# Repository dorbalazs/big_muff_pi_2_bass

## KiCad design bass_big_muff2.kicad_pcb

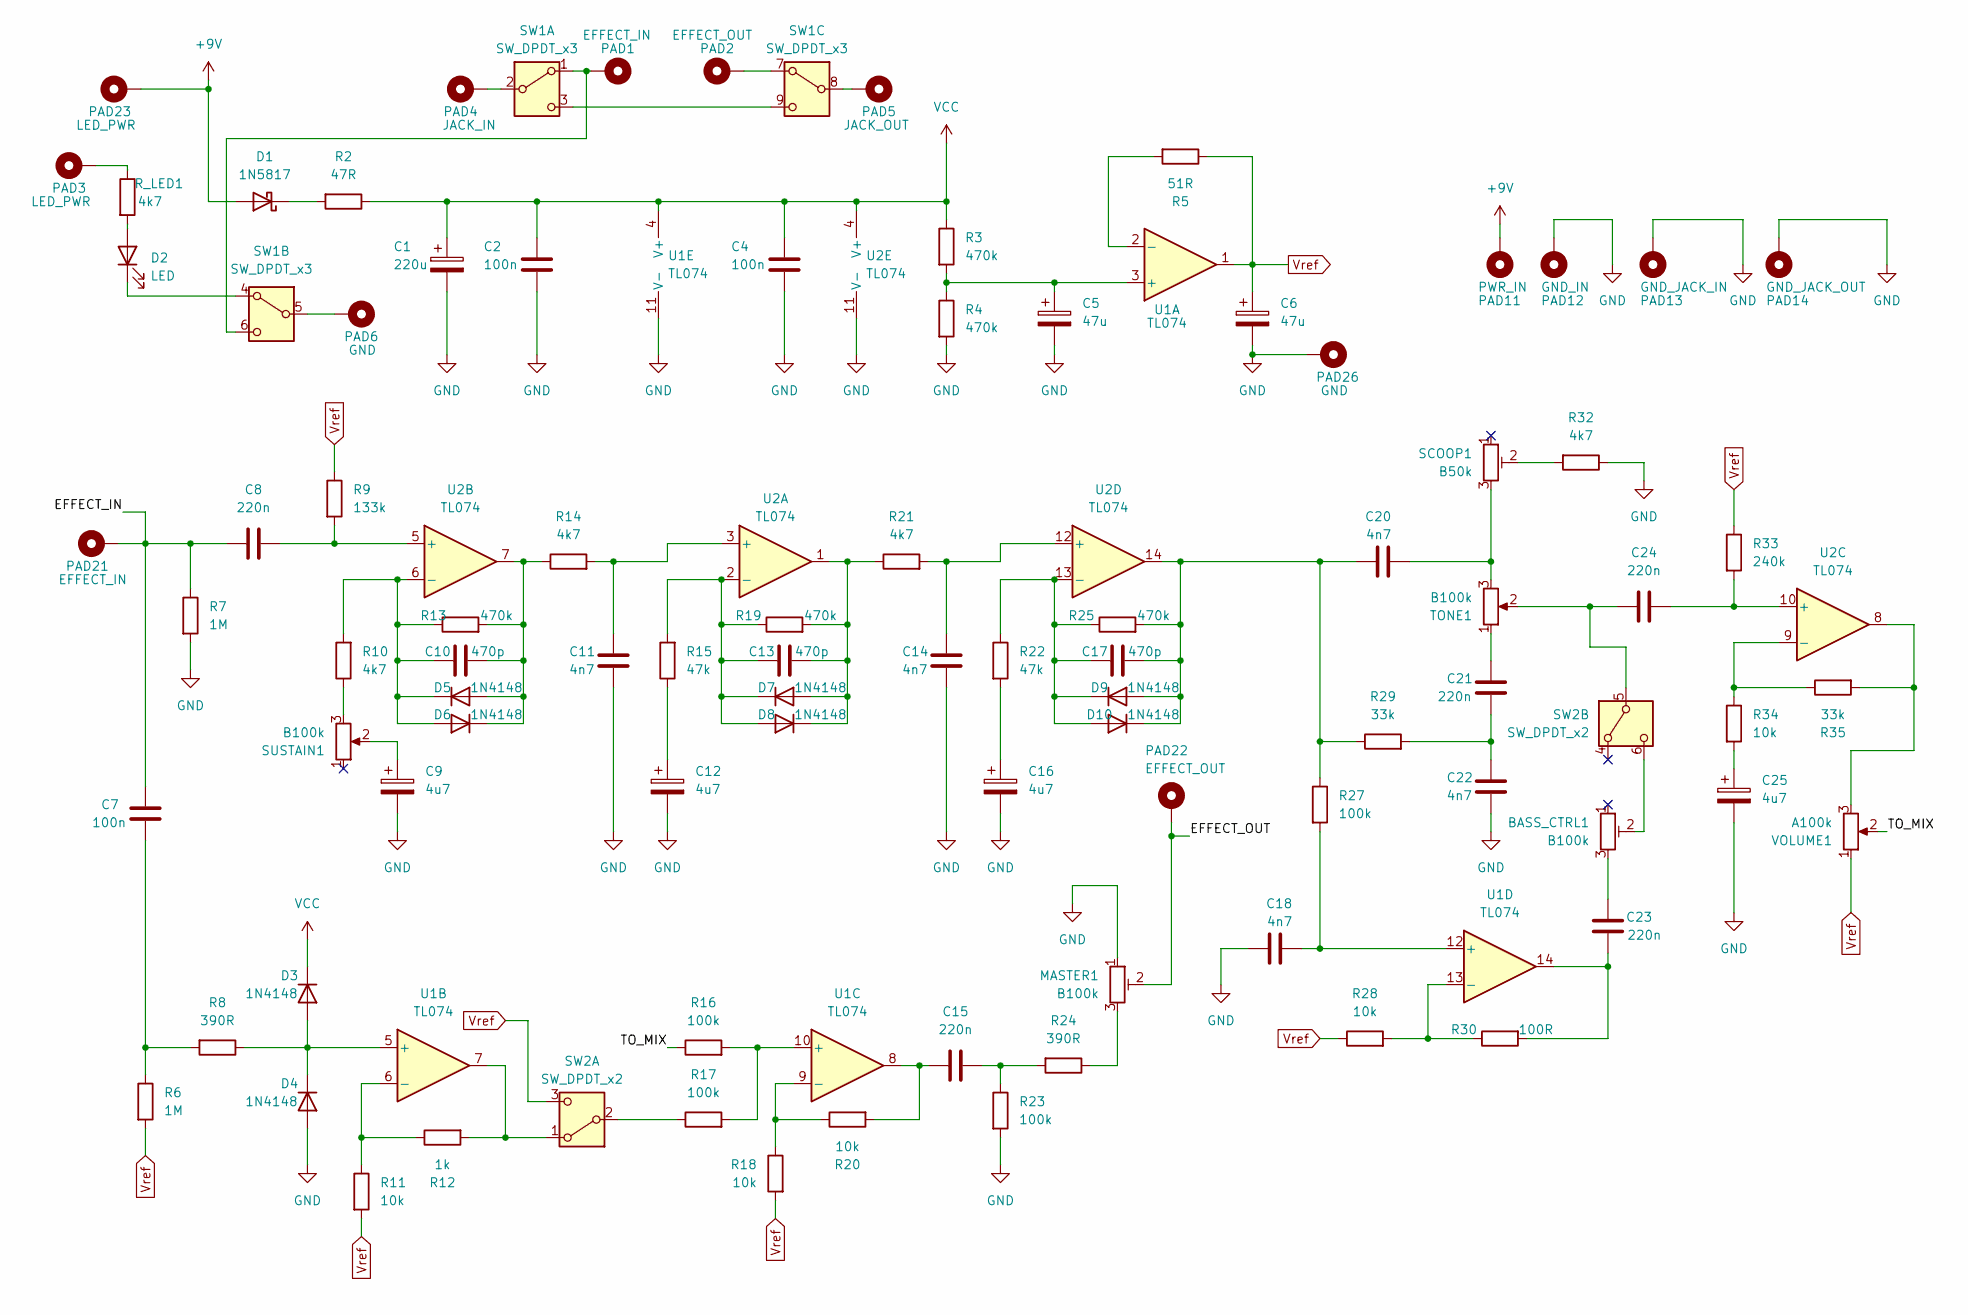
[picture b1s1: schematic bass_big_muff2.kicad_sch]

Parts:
BASS_CTRL1: B100k; Potentiometer_Runtron_RM-065_Vertical
C1: 220u; CP_Radial_D6.3mm_P2.50mm
C2, C4: 100n; C_Disc_D5.0mm_W2.5mm_P2.50mm
C5, C6: 47u; CP_Radial_D5.0mm_P2.50mm
C7: 100n; C_Rect_L7.2mm_W3.5mm_P5.00mm
C8, C15, C21, C23, C24: 220n; C_Rect_L7.2mm_W3.5mm_P5.00mm
C9, C12, C16, C25: 4u7; CP_Radial_D4.0mm_P1.50mm
C10, C13, C17: 470p; C_Disc_D3.4mm_W2.1mm_P2.50mm
C11, C14, C18, C20, C22: 4n7; C_Rect_L7.2mm_W2.5mm_P5.00mm
D1: 1N5817; D_DO-41_SOD81_P10.16mm_Horizontal
D2: LED; LED_D5.0mm
D3, D4, D5, D6, D7, D8, D9, D10: 1N4148; D_DO-35_SOD27_P7.62mm_Horizontal
MASTER1: B100k; Potentiometer_Runtron_RM-065_Vertical
PAD1, PAD21: EFFECT_IN; SolderWire-0.5sqmm_1x01_D0.9mm_OD2.1mm
PAD2, PAD22: EFFECT_OUT; SolderWire-0.5sqmm_1x01_D0.9mm_OD2.1mm
PAD3, PAD23: LED_PWR; SolderWire-0.5sqmm_1x01_D0.9mm_OD2.1mm
PAD4: JACK_IN; SolderWire-0.5sqmm_1x01_D0.9mm_OD2.1mm
PAD5: JACK_OUT; SolderWire-0.5sqmm_1x01_D0.9mm_OD2.1mm
PAD6, PAD26: GND; SolderWire-0.5sqmm_1x01_D0.9mm_OD2.1mm
PAD11: PWR_IN; SolderWire-0.5sqmm_1x01_D0.9mm_OD2.1mm
PAD12: GND_IN; SolderWire-0.5sqmm_1x01_D0.9mm_OD2.1mm
PAD13: GND_JACK_IN; SolderWire-0.5sqmm_1x01_D0.9mm_OD2.1mm
PAD14: GND_JACK_OUT; SolderWire-0.5sqmm_1x01_D0.9mm_OD2.1mm
R2: 47R; R_Axial_DIN0207_L6.3mm_D2.5mm_P7.62mm_Horizontal
R3, R4, R25: 470k; R_Axial_DIN0207_L6.3mm_D2.5mm_P7.62mm_Horizontal
R5: 51R; R_Axial_DIN0207_L6.3mm_D2.5mm_P7.62mm_Horizontal
R6, R7: 1M; R_Axial_DIN0207_L6.3mm_D2.5mm_P7.62mm_Horizontal
R8, R24: 390R; R_Axial_DIN0207_L6.3mm_D2.5mm_P7.62mm_Horizontal
R9: 133k; R_Axial_DIN0207_L6.3mm_D2.5mm_P2.54mm_Vertical
R10, R14, R32: 4k7; R_Axial_DIN0207_L6.3mm_D2.5mm_P2.54mm_Vertical
R11, R34: 10k; R_Axial_DIN0207_L6.3mm_D2.5mm_P7.62mm_Horizontal
R12: 1k; R_Axial_DIN0207_L6.3mm_D2.5mm_P7.62mm_Horizontal
R13, R19: 470k; R_Axial_DIN0207_L6.3mm_D2.5mm_P2.54mm_Vertical
R15: 47k; R_Axial_DIN0207_L6.3mm_D2.5mm_P2.54mm_Vertical
R16, R17: 100k; R_Axial_DIN0207_L6.3mm_D2.5mm_P2.54mm_Vertical
R18, R20, R28: 10k; R_Axial_DIN0207_L6.3mm_D2.5mm_P2.54mm_Vertical
R21: 4k7; R_Axial_DIN0207_L6.3mm_D2.5mm_P7.62mm_Horizontal
R22: 47k; R_Axial_DIN0207_L6.3mm_D2.5mm_P7.62mm_Horizontal
R23, R27: 100k; R_Axial_DIN0207_L6.3mm_D2.5mm_P7.62mm_Horizontal
R29, R35: 33k; R_Axial_DIN0207_L6.3mm_D2.5mm_P7.62mm_Horizontal
R30: 100R; R_Axial_DIN0207_L6.3mm_D2.5mm_P2.54mm_Vertical
R33: 240k; R_Axial_DIN0207_L6.3mm_D2.5mm_P7.62mm_Horizontal
R_LED1: 4k7; R_Axial_DIN0207_L6.3mm_D2.5mm_P7.62mm_Horizontal
SCOOP1: B50k; Potentiometer_Runtron_RM-065_Vertical
SUSTAIN1: B100k; POM1615
SW1: SW_DPDT_x3; 3PDT-M12
SW2: SW_DPDT_x2; TSM202
TONE1: B100k; POM1615
U1, U2: TL074; DIP-14_W7.62mm_Socket
VOLUME1: A100k; POM1615

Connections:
+9V: D1.2 (A), PAD11.1 (1_1), PAD23.1 (1_1)
/EFFECT_IN: C7.1, C8.2, PAD21.1 (1_1), R7.1
/EFFECT_OUT: MASTER1.2, PAD22.1 (1_1)
/TO_MIX: R16.1, VOLUME1.2
GND: C1.2, C2.2, C4.2, C5.2, C6.2, C9.2, C11.2, C12.2, C14.2, C16.2, C18.1, C22.2, C25.2, D4.2 (A), MASTER1.1, PAD12.1 (1_1), PAD13.1 (1_1), PAD14.1 (1_1), PAD26.1 (1_1), R4.2, R7.2, R23.2, R32.1, U1.11 (V-), U2.11 (V-)
unnamed: BASS_CTRL1.3, C23.1
unnamed: C7.2, R6.1, R8.2
unnamed: C9.1, SUSTAIN1.2
unnamed: C12.1, R15.1
unnamed: C15.1, R23.1, R24.2
unnamed: C15.2, R20.2, U1.8
unnamed: C16.1, R22.2
unnamed: C20.2, SCOOP1.3, TONE1.3
unnamed: C21.1, TONE1.1
unnamed: C21.2, C22.1, R29.2
unnamed: C23.2, R30.2, U1.14
unnamed: C25.1, R34.2
unnamed: D1.1 (K), R2.2
unnamed: D2.2 (A), R_LED1.2
unnamed: D2.1 (K), SW1.4 (A)
unnamed: D3.2 (A), D4.1 (K), R8.1, U1.5 (+)
unnamed: C10.2, D5.2 (A), D6.1 (K), R13.2, R14.1, U2.7
unnamed: C10.1, D5.1 (K), D6.2 (A), R10.2, R13.1, U2.6 (-)
unnamed: C13.2, D7.2 (A), D8.1 (K), R19.2, R21.1, U2.1
unnamed: C13.1, D7.1 (K), D8.2 (A), R15.2, R19.1, U2.2 (-)
unnamed: C17.1, D9.1 (K), D10.2 (A), R22.1, R25.1, U2.13 (-)
unnamed: C17.2, C20.1, D9.2 (A), D10.1 (K), R25.2, R27.1, R29.1, U2.14
unnamed: MASTER1.3, R24.1
unnamed: PAD3.1 (1_1), R_LED1.1
unnamed: R10.1, SUSTAIN1.3
unnamed: R32.2, SCOOP1.2
unnamed: R35.2, U2.8, VOLUME1.3
unnamed: PAD1.1 (1_1), SW1.1 (A), SW1.6 (C)
unnamed: PAD4.1 (1_1), SW1.2 (B)
unnamed: SW1.3 (C), SW1.9 (C)
unnamed: PAD6.1 (1_1), SW1.5 (B)
unnamed: PAD2.1 (1_1), SW1.7 (A)
unnamed: PAD5.1 (1_1), SW1.8 (B)
unnamed: R12.2, SW2.1 (A), U1.7
unnamed: R17.1, SW2.2 (B)
unnamed: C24.2, SW2.5 (B), TONE1.2
unnamed: BASS_CTRL1.2, SW2.6 (C)
unnamed: C5.1, R3.2, R4.1, U1.3 (+)
unnamed: R5.2, U1.2 (-)
unnamed: R11.1, R12.1, U1.6 (-)
unnamed: R16.2, R17.2, U1.10 (+)
unnamed: R18.1, R20.1, U1.9 (-)
unnamed: C18.2, R27.2, U1.12 (+)
unnamed: R28.2, R30.1, U1.13 (-)
unnamed: C11.1, R14.2, U2.3 (+)
unnamed: C8.1, R9.2, U2.5 (+)
unnamed: C24.1, R33.2, U2.10 (+)
unnamed: R34.1, R35.1, U2.9 (-)
unnamed: C14.1, R21.2, U2.12 (+)
VCC: C1.1, C2.1, C4.1, D3.1 (K), R2.1, R3.1, U1.4 (V+), U2.4 (V+)
Vref: C6.1, R5.1, R6.2, R9.1, R11.2, R18.2, R28.1, R33.1, SW2.3 (C), U1.1, VOLUME1.1

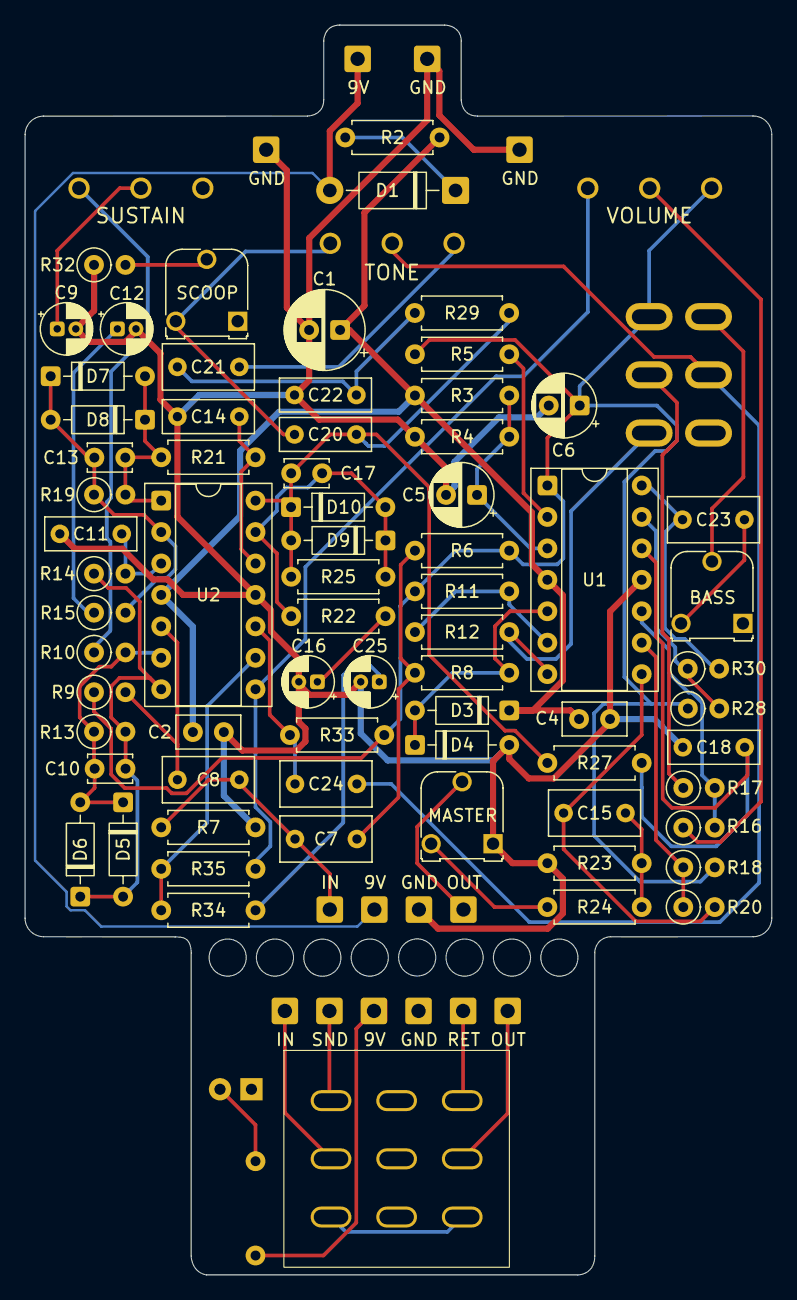
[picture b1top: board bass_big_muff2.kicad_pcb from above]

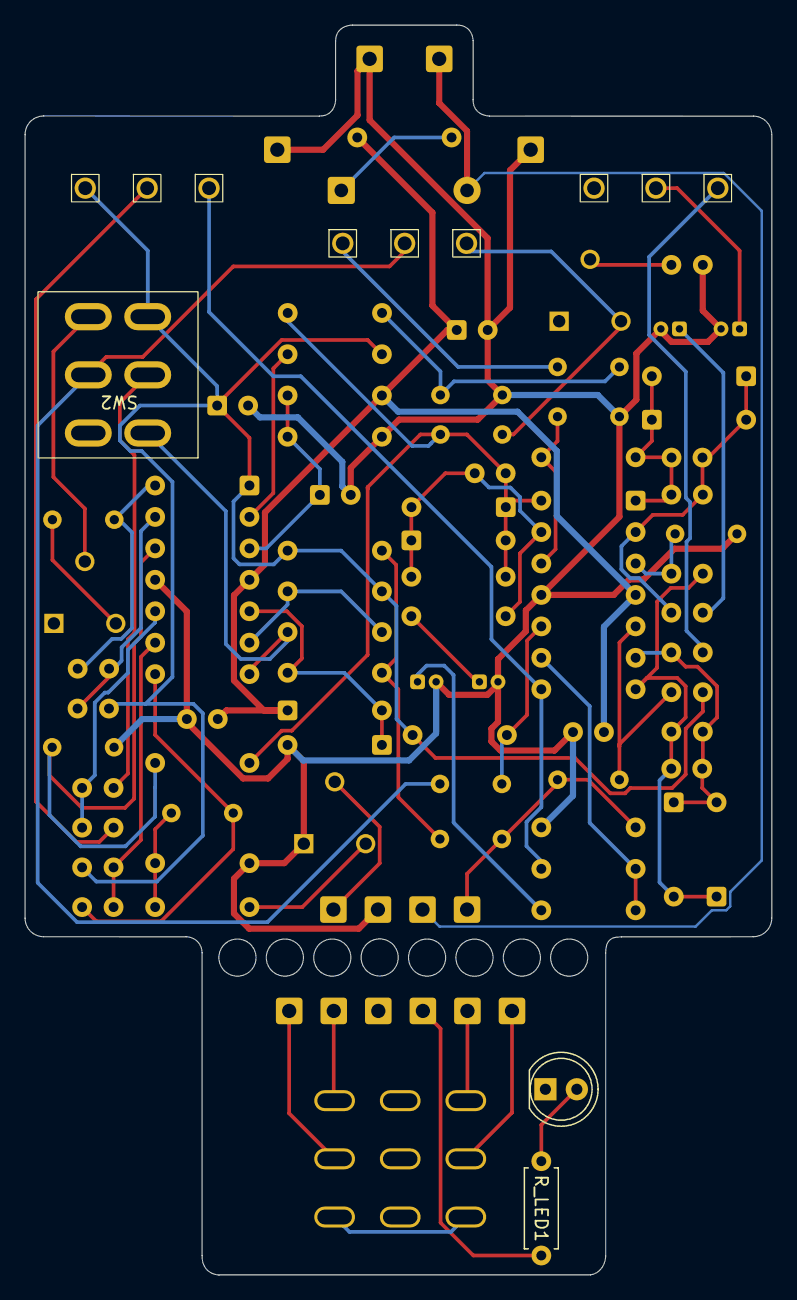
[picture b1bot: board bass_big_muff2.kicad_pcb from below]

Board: 2 copper layers, 60.3 x 101.0 mm, 90 parts (6 on the bottom side), 56 nets.
